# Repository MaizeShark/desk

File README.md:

# Desk

A custom-built smart L-shaped desk with deep Home Assistant integration. The project spans hardware design (custom PCBs), embedded firmware (ESP32-S3), and software services, all tied together via MQTT.

## Overview

This repository contains all the design files and software for a DIY smart desk ecosystem. The desk houses a dedicated electronics enclosure that handles audio routing, thermal management, environmental monitoring, and a media display — all controllable from Home Assistant.

```
desk/
├── PCB/            # Main KiCad PCB & schematics (ESP32-S3, DSP, DACs, PSU, …)
├── HID/            # Input device PCBs (rotary encoders, HID controller)
├── audio.md        # Audio matrix design document
├── fan_control.md  # Fan controller design document
├── Raspi/          # MPRIS-to-MQTT bridge service (Python, systemd)
└── UI/Docker/      # Media artwork generator & HTTP server (Docker)
```

---

## Sub-Projects

| | |
|---|---|
| [Audio Matrix](audio.md) | 6-in / 4-out digital audio matrix at 96 kHz / 24-bit. ADAU1451 DSP with ASRC, controlled by ESP32-S3 over I²C. Sources include USB, S/PDIF, Bluetooth (LDAC), I²S, and analog line-in. |
| [Fan Controller](fan_control.md) | ESP32-S3 reads all component temperatures via a TI TMP468 and the Raspberry Pi's CPU temp over I²C, then drives an Arctic P8 Max PWM fan based on the system hotspot. |
| [Desk GUI](https://github.com/MaizeShark/desk-gui) | ESP32-S3 firmware (PlatformIO / LVGL) for the 4-inch touchscreen control panel. Shows current track and album art, Spotify playback controls, and drives 12× addressable RGB LEDs. |
| [MPRIS → MQTT](Raspi/) | Python systemd service on the Raspberry Pi that watches the active media player via D-Bus and publishes playback state to MQTT. See [`Raspi/README.md`](Raspi/README.md). |
| [Media Artwork Service](UI/Docker/) | Dockerised service that fetches album art from Spotify / Jellyfin, composites a 480×320 image, serves it over HTTP, and publishes the URL to MQTT. See [`UI/Docker/README.md`](UI/Docker/README.md). |

---

## Hardware

The main PCB (`PCB/Tisch.kicad_pcb`) integrates all of the above subsystems onto a single board. Schematics are split into logical sheets:

| File | Content |
|---|---|
| `esp32.kicad_sch` | Main ESP32-S3 controller |
| `ADAU1451.kicad_sch` | DSP |
| `dac.kicad_sch` | PCM5122 DAC outputs |
| `adc.kicad_sch` | PCM1809 ADC input |
| `QCC5125.kicad_sch` | Bluetooth RX |
| `bm83.kicad_sch` | Bluetooth TX |
| `spdif.kicad_sch` | S/PDIF receiver |
| `raspi.kicad_sch` | Raspberry Pi interface |
| `fan.kicad_sch` | Fan control circuit |
| `psu.kicad_sch` | Power supply |
| `display.kicad_sch` | Display connector |
| `hid.kicad_sch` | HID / encoder inputs |

The `HID/` directory contains a separate PCB for the rotary encoder input device.

---

## License

This project is licensed under the **GNU General Public License v3.0**. See [`LICENSE`](LICENSE) for details.

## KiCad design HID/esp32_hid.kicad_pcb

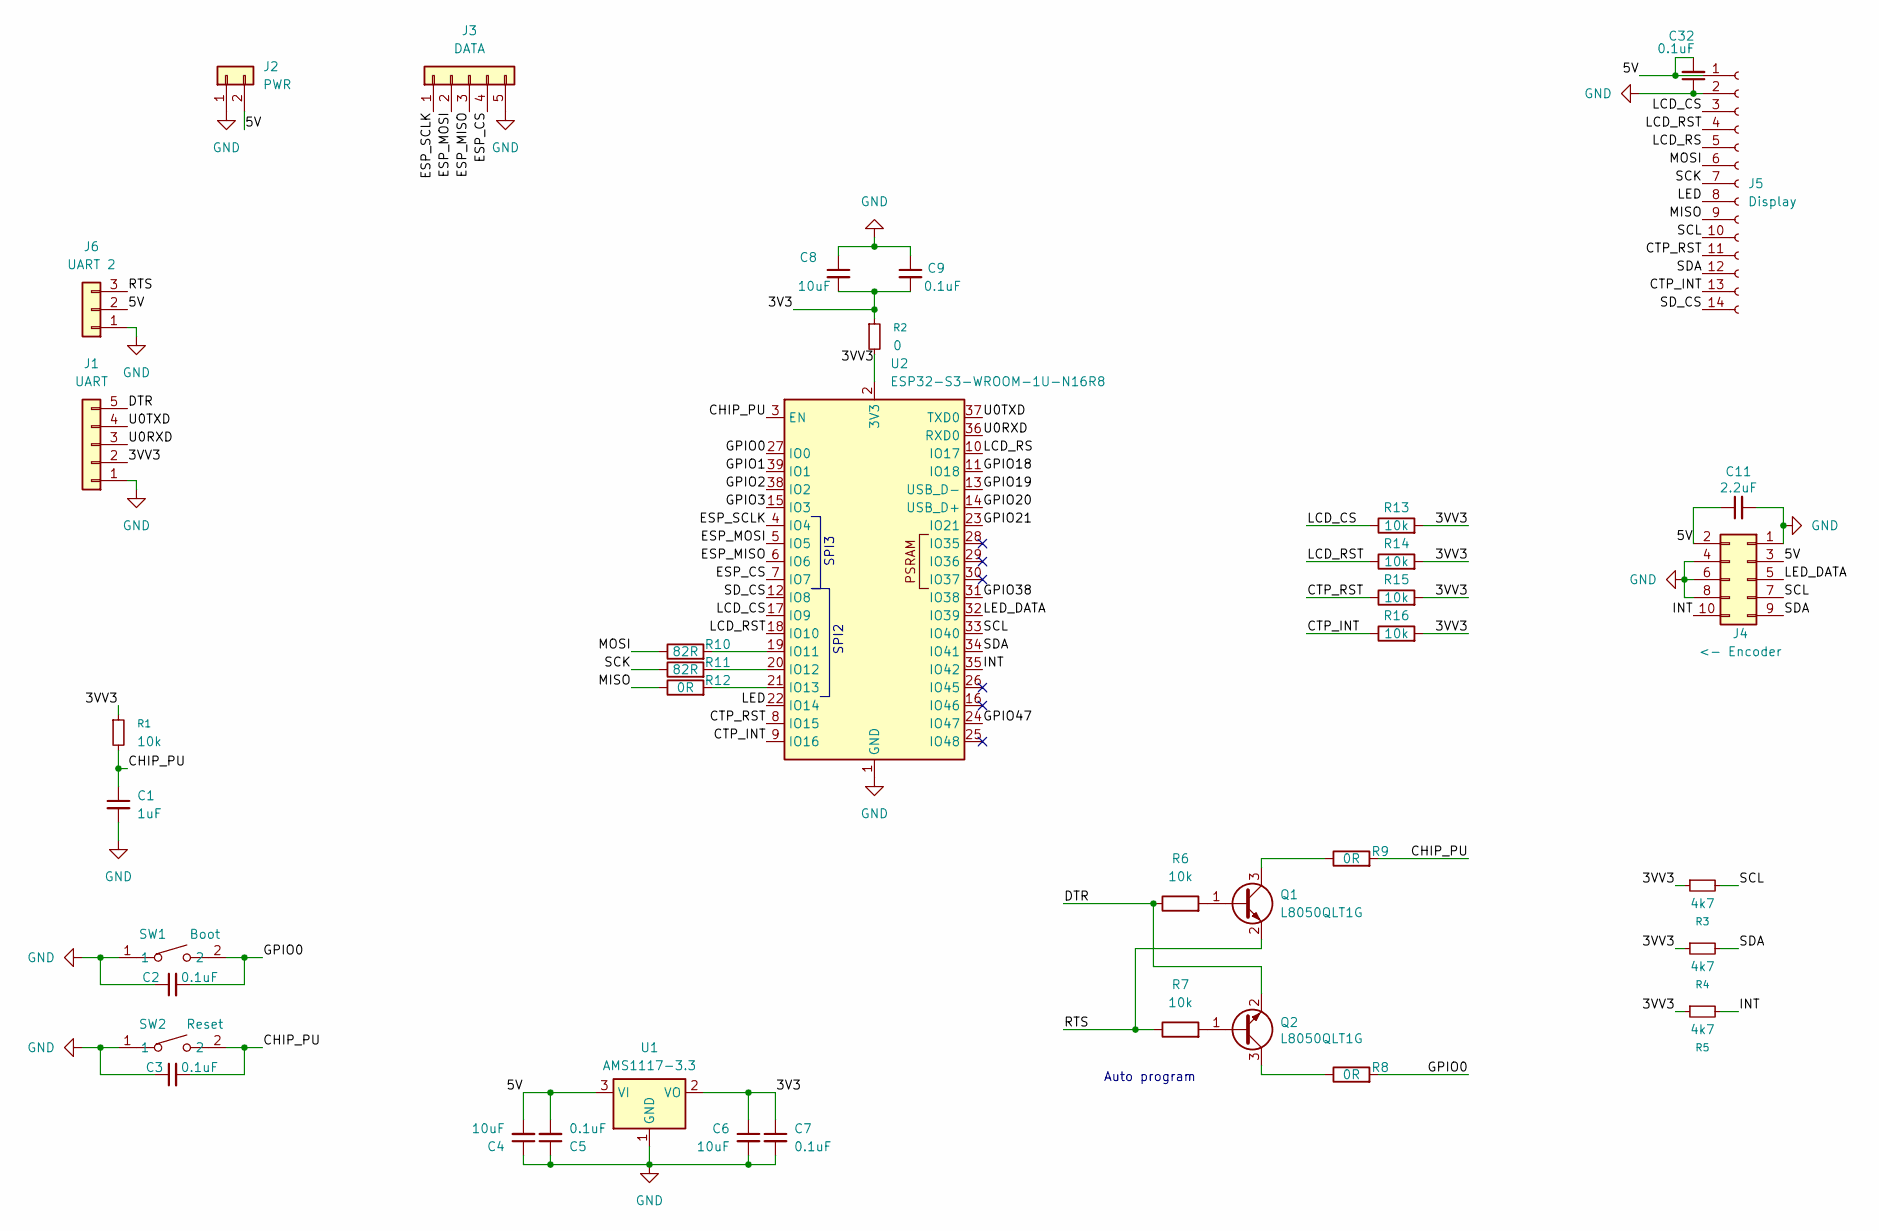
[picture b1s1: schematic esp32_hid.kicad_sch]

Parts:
C1: 1uF; C_0603_1608Metric
C2, C3, C5, C7, C9, C32: 0.1uF; C_0603_1608Metric
C4, C6, C8: 10uF; C_0805_2012Metric
C11: 2.2uF; C_0603_1608Metric
J1: UART; PinHeader_1x05_P2.54mm_Vertical
J2: PWR; JST_XH_B2B-XH-A_1x02_P2.50mm_Vertical
J3: DATA; JST_XH_B5B-XH-A_1x05_P2.50mm_Vertical
J4: <- Encoder; JST_PHD_B10B-PHDSS_2x05_P2.00mm_Vertical; LCSC C471519
J5: Display; PinSocket_1x14_P2.54mm_Vertical
J6: UART 2; PinHeader_1x03_P2.54mm_Vertical
Q1, Q2: L8050QLT1G; SOT-23; LCSC C49581
R1: 10k; R_0603_1608Metric
R2: 0; R_0603_1608Metric
R3, R4, R5: 4k7; R_0603_1608Metric
R6, R7, R13, R14, R15, R16: 10k; R_0603_1608Metric; LCSC C25804
R8, R9, R12: 0R; R_0603_1608Metric; LCSC C95177
R10, R11: 82R; R_0603_1608Metric; LCSC C23255
SW1: Boot; SW-SMD_L3.9-W3.0-P4.45; LCSC Part C720477
SW2: Reset; SW-SMD_L3.9-W3.0-P4.45; LCSC Part C720477
U1: AMS1117-3.3; SOT-223-3_TabPin2
U2: ESP32-S3-WROOM-1U-N16R8; ESP32-S3-WROOM-1

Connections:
/3V3: C6.1, C7.1, C8.2, C9.2, R2.1, U1.2 (VO)
/3VV3: J1.2, R1.1, R2.2, R3.1, R4.1, R5.1, R13.2, R14.2, R15.2, R16.2, U2.2 (3V3)
/5V: C4.2, C5.2, C11.1, C32.2, J2.2, J4.2, J4.3, J5.1, J6.2, U1.3 (VI)
/CHIP_PU: C1.1, C3.2, R1.2, R9.2, SW2.2, U2.3 (EN)
/CTP_INT: J5.13, R16.1, U2.9 (IO16)
/CTP_RST: J5.11, R15.1, U2.8 (IO15)
/DTR: J1.5, Q2.2 (E), R6.1
/ESP_CS: J3.4, U2.7 (IO7)
/ESP_MISO: J3.3, U2.6 (IO6)
/ESP_MOSI: J3.2, U2.5 (IO5)
/ESP_SCLK: J3.1, U2.4 (IO4)
/GPIO0: C2.2, R8.2, SW1.2, U2.27 (IO0)
/GPIO1: U2.39 (IO1)
/GPIO2: U2.38 (IO2)
/GPIO3: U2.15 (IO3)
/GPIO18: U2.11 (IO18)
/GPIO19: U2.13 (USB_D-)
/GPIO20: U2.14 (USB_D+)
/GPIO21: U2.23 (IO21)
/GPIO38: U2.31 (IO38)
/GPIO47: U2.24 (IO47)
/INT: J4.10, R5.2, U2.35 (IO42)
/LCD_CS: J5.3, R13.1, U2.17 (IO9)
/LCD_RS: J5.5, U2.10 (IO17)
/LCD_RST: J5.4, R14.1, U2.18 (IO10)
/LED: J5.8, U2.22 (IO14)
/LED_DATA: J4.5, U2.32 (IO39)
/MISO: J5.9, R12.1
/MOSI: J5.6, R10.1
/RTS: J6.3, Q1.2 (E), R7.1
/SCK: J5.7, R11.1
/SCL: J4.7, J5.10, R3.2, U2.33 (IO40)
/SDA: J4.9, J5.12, R4.2, U2.34 (IO41)
/SD_CS: J5.14, U2.12 (IO8)
/U0RXD: J1.3, U2.36 (RXD0)
/U0TXD: J1.4, U2.37 (TXD0)
GND: C1.2, C2.1, C3.1, C4.1, C5.1, C6.2, C7.2, C8.1, C9.1, C11.2, C32.1, J1.1, J2.1, J3.5, J4.1, J4.4, J4.6, J4.8, J5.2, J6.1, SW1.1, SW2.1, U1.1 (GND), U2.1 (GND), U2.40 (GND), U2.41 (GND)
unnamed: Q1.1 (B), R6.2
unnamed: Q1.3 (C), R9.1
unnamed: Q2.1 (B), R7.2
unnamed: Q2.3 (C), R8.1
unnamed: R10.2, U2.19 (IO11)
unnamed: R11.2, U2.20 (IO12)
unnamed: R12.2, U2.21 (IO13)

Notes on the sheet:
Auto program
SPI2
SPI3

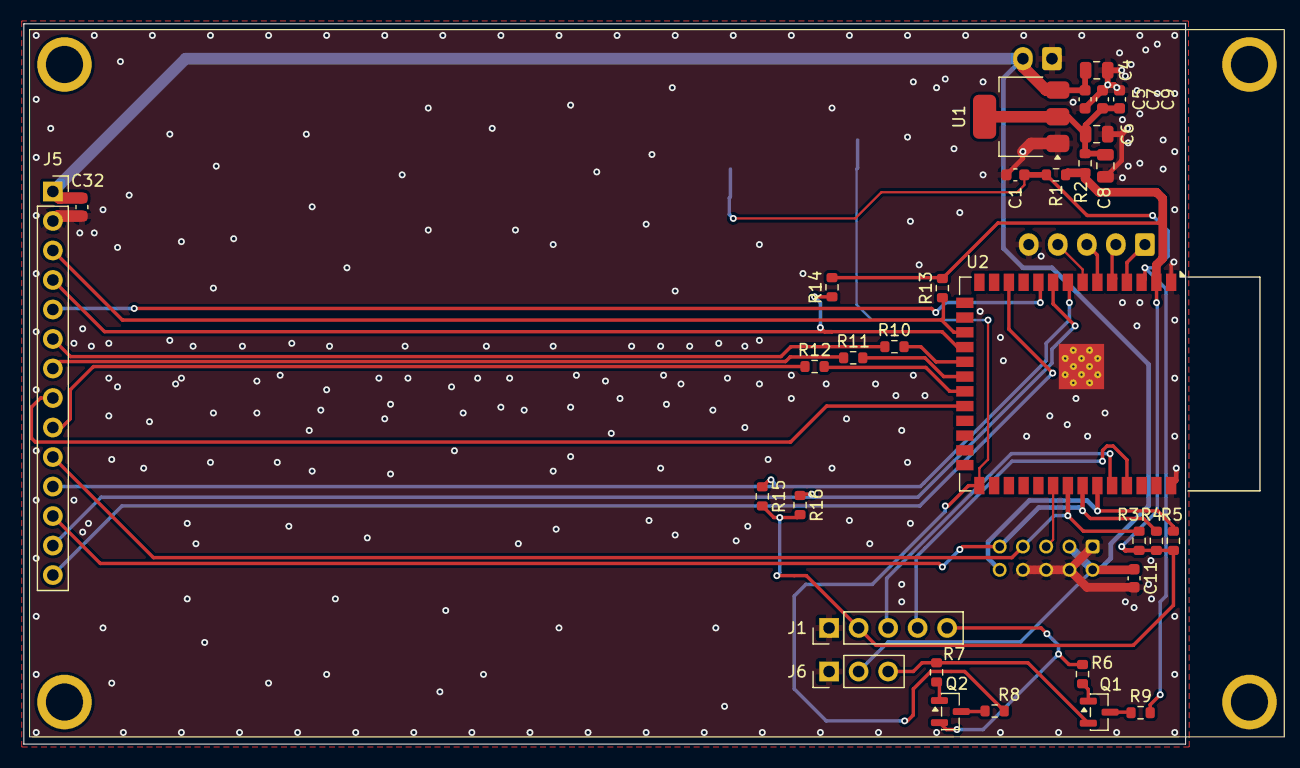
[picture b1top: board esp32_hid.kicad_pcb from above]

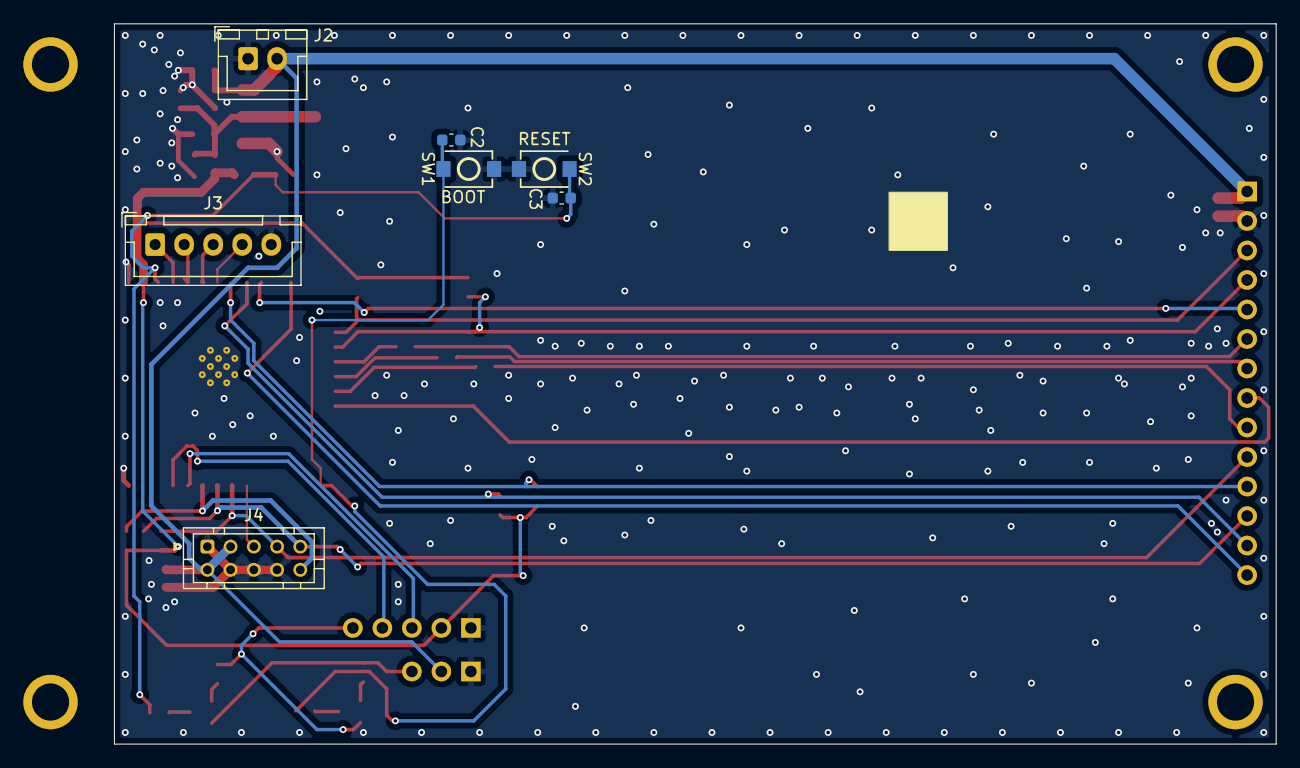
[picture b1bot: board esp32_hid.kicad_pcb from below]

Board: 2 copper layers, 100.0 x 62.0 mm, 39 parts (7 on the bottom side), 35 nets.

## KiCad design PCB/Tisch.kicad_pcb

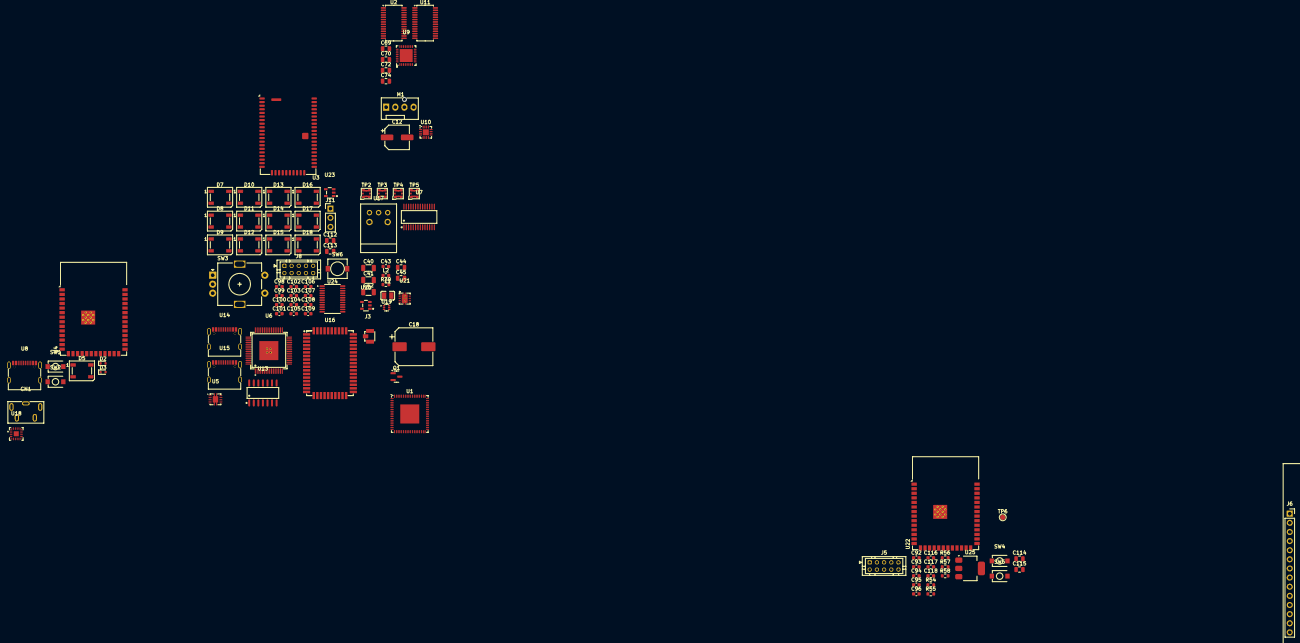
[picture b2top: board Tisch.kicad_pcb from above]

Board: 2 copper layers, 102 parts (0 on the bottom side), 82 nets, no tracks yet.

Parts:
C12: 47uF; CP_Elec_6.3x5.4
C18: 100uF; CP_Elec_10x10
C40, C41, C42: 10uF; C_1206_3216Metric
C43, C118: 2.2uF; C_0603_1608Metric
C44, C45, C112, C113, C114, C115: 10uF; C_0805_2012Metric
C69, C70, C72, C74: 2.2uF; C_0805_2012Metric
C92, C94, C95, C96, C98, C99, C100, C101, C102, C103, C104, C105, C106, C107, C108, C109, C116, C117: 0.1uF; C_0603_1608Metric
C93: 1uF; C_0603_1608Metric
CN1: PJ-358H-B; AUDIO-TH_PJ-358H-B
D2, D3: LESD5D5.0CT1G; D_SOD-523
D5, D7, D8, D9, D10, D11, D12, D13, D14, D15, D16, D17, D18: WS2812B; LED_WS2812B_PLCC4_5.0x5.0mm_P3.2mm
J3: BT1 Ant; ANT-SMD_UFL-R-SMT-1-10
J5: <- Encoder; JST_PHD_B10B-PHDSS_2x05_P2.00mm_Vertical
J6: Display; PinSocket_1x14_P2.54mm_Vertical
J8: ->ESP32; JST_PHD_B10B-PHDSS_2x05_P2.00mm_Vertical
J11: OPT; PinHeader_1x03_P2.54mm_Vertical
L1: 1uH; L0806
L2: 150nH; L_0603_1608Metric
M1: P8 Max; FanPinHeader_1x04_P2.54mm_Vertical
Q1: AO3400A; SOT-23
R30: 330m; R_0603_1608Metric
R54: 10k; R_0603_1608Metric
R55: 0; R_0603_1608Metric
R56, R57, R58: 4k7; R_0603_1608Metric
SW1, SW4: Boot; SW-SMD_L3.9-W3.0-P4.45
SW2, SW5: Reset; SW-SMD_L3.9-W3.0-P4.45
SW3: EC11E15244B2; RotaryEncoder_Alps_EC11E-Switch_Vertical_H20mm
SW6: SKSUAAE010; KEY-SMD_SKSUAAE010
TP2: spdif_error; CoaxialSwitch_Hirose_MS-156C3_Horizontal
TP3: spdif_audio; CoaxialSwitch_Hirose_MS-156C3_Horizontal
TP4: spdif_fsout0; CoaxialSwitch_Hirose_MS-156C3_Horizontal
TP5: spdif_fsout1; CoaxialSwitch_Hirose_MS-156C3_Horizontal
TP6: LED_D; TestPoint_Pad_D1.5mm
U1: ADAU1451; LFCSP-72-1EP_10x10mm_P0.5mm_EP5.3x5.3mm
U2, U11: PCM5122PW; TSSOP-28_4.4x9.7mm_P0.65mm
U3: Microchip_BM83
U4: ESP32-S3-WROOM-1
U5: TS3USB221DRCR; VSON-10_L3.0-W3.0-P0.50-TL-EP_TPS62410DRCR
U6: XU208-128-TQ64-C10; TQFP-64_L10.0-W10.0-P0.50-LS12.0-BL-EP5.3
U7: DIR9001PWR; TSSOP-28_L9.7-W4.4-P0.65-LS6.4-BL
U8, U14, U15: GT-USB-7010ASV; USB-C-SMD_G-SWITCH_GT-USB-7010ASV
U9: PCM5242RHBR; VQFN-32_L5.0-W5.0-P0.50-BL-EP
U10: TMP468xxRGT; VQFN-16-1EP_3x3mm_P0.5mm_EP1.68x1.68mm
U13: CD74HC02M96; SOIC-14_L8.7-W3.9-P1.27-LS6.0-BL
U16: BTM525; SJR-BTM525
U17: PLR237/T10BK; OPTO-TH_PLR237-T10BK
U18: PCM1809IRTER; WQFN-20_L3.0-W3.0-P0.50-TL-EP1.4
U19: TPS62A02NADRL; SOT-563
U20, U23: TPS7B92033DBVR; SOT-23-5_L2.9-W1.6-P0.95-LS2.8-BR
U21: TPS7A9401DSCR; WSON-10_L3.0-W3.0-P0.50-TL-EP
U22: ESP32-S3-WROOM-1U-N16R8; ESP32-S3-WROOM-1
U24: TCA9535PWR; TSSOP-24_4.4x7.8mm_P0.65mm
U25: AMS1117-3.3; SOT-223-3_TabPin2

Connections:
+3V3: U5.10 (VCC), U13.14 (VCC)
+5V: D5.1 (VDD), L2.1, U20.1 (IN), U21.1 (IN), U21.2 (IN)
+12V: C12.1, M1.2 (+)
/ADC/Left Audio: CN1.2 (Tip), U18.1 (IN1P)
/ADC/Right Audio: CN1.5 (Ring), U18.3 (IN2P)
/DAC/LDOO: U2.26 (LDOO), U11.26 (LDOO)
/DAC/SCL: U2.12 (SCL/MC/ATT1), U9.18 (SCL/MC/ATT1), U11.12 (SCL/MC/ATT1)
/DAC/SDA: U2.11 (SDA/MOSI/ATT2), U9.17 (SDA/MOSI/ATT2), U11.11 (SDA/MOSI/ATT2)
/ESP32/CHIP_PU: SW2.2, U4.3 (EN)
/ESP32/GPIO0: SW1.2, U4.27 (IO0)
/ESP32/GPIO19: D2.2 (A2), U4.13 (USB_D-), U8.A7 (DN1), U8.B7 (DN2)
/ESP32/GPIO20: D3.2 (A2), U4.14 (USB_D+), U8.A6 (DP1), U8.B6 (DP2)
/HID/ESP32 HID/3V3: C92.2, C94.2, C115.1, C117.1, R54.1, R55.1, U25.2 (VO)
/HID/ESP32 HID/5V: C114.2, C116.2, C118.1, J5.1, J6.1, U25.3 (VI)
/HID/ESP32 HID/CHIP_PU: C93.1, C96.2, R54.2, SW5.2, U22.3 (EN)
/HID/ESP32 HID/CTP_INT: J6.13, U22.9 (IO16)
/HID/ESP32 HID/CTP_RST: J6.11, U22.8 (IO15)
/HID/ESP32 HID/GPIO0: C95.2, SW4.2
/HID/ESP32 HID/INT: J5.9, R58.2, U22.35 (IO42)
/HID/ESP32 HID/LCD_CS: J6.3, U22.17 (IO9)
/HID/ESP32 HID/LCD_RST: J6.4, U22.18 (IO10)
/HID/ESP32 HID/LED: J6.8, U22.22 (IO14)
/HID/ESP32 HID/LED_DATA: J5.3, TP6.1, U22.32 (IO39)
/HID/ESP32 HID/MISO: J6.9, U22.19 (IO11)
/HID/ESP32 HID/MOSI: J6.6, U22.20 (IO12)
/HID/ESP32 HID/SCK: J6.7, U22.21 (IO13)
/HID/ESP32 HID/SCL: J5.5, J6.10, R56.2, U22.33 (IO40)
/HID/ESP32 HID/SDA: J5.7, J6.12, R57.2, U22.34 (IO41)
/HID/ESP32 HID/SD_CS: J6.14, U22.12 (IO8)
/HID/ESP32 HID/VCC_3V3: R56.1, R57.1, R58.1
/HID/Encoder/3V3: C113.1, U23.5 (OUT)
/HID/Encoder/5V: C98.1, C99.1, C100.1, C101.1, C102.1, C103.1, C104.1, C105.1, C106.1, C107.1, C108.1, C109.1, C112.2, D7.1 (VDD), D8.1 (VDD), D9.1 (VDD), D10.1 (VDD), D11.1 (VDD), D12.1 (VDD), D13.1 (VDD), D14.1 (VDD), D15.1 (VDD), D16.1 (VDD), D17.1 (VDD), D18.1 (VDD), J8.1, U23.1 (IN)
/HID/Encoder/INT: J8.9, U24.1 (~INT)
/HID/Encoder/LED_DATA: D7.4 (DIN), J8.3
/HID/Encoder/SCL: J8.5, U24.22 (SCL)
/HID/Encoder/SDA: J8.7, U24.23 (SDA)
/HID/Encoder/back_sw: SW6.1, U24.7 (P03)
/HID/Encoder/rot_a: SW3.A, U24.4 (P00)
/HID/Encoder/rot_b: SW3.B, U24.5 (P01)
/HID/Encoder/rot_sw: SW3.S1, U24.6 (P02)
/QCC5125/RF_ANT_50R: J3.1 (In), U16.46 (RF)
/SPdif/SPDIF: U7.20 (RXIN), U17.3 (VOUT)
/USB audio/1D+: U5.1 (1D+), U14.A6 (DP1), U14.B6 (DP2)
/USB audio/1D-: U5.2 (1D-), U14.A7 (DN1), U14.B7 (DN2)
/USB audio/2D+: U5.3 (2D+), U15.A6 (DP1), U15.B6 (DP2)
/USB audio/2D-: U5.4 (2D-), U15.A7 (DN1), U15.B7 (DN2)
AVDD_3V3: C72.1, U2.8 (AVDD), U7.24 (VCC), U9.5 (CPVDD), U9.14 (AVDD), U11.8 (AVDD), U17.1 (VCC), U18.16 (AVDD), U21.8 (SNS), U21.9 (OUT), U21.10 (OUT)
DVDD_3V3: C40.1, C41.1, C42.1, L1.2, U2.18 (MODE2/MS), U2.28 (DVDD), U3.23 (BAT_IN), U9.22 (ADR2/GPIO2/GPO), U9.24 (MODE2/MS), U11.16 (ADR2/GPIO2/DOUT), U11.18 (MODE2/MS), U11.24 (ADR1/MISO/FMT), U11.28 (DVDD), U19.6 (OUT)
GND: C12.2, C18.2, C40.2, C41.2, C42.2, C43.2, C44.2, C45.2, C70.1, C72.2, C74.1, C92.1, C93.2, C94.1, C95.1, C96.1, C98.2, C99.2, C100.2, C101.2, C102.2, C103.2, C104.2, C105.2, C106.2, C107.2, C108.2, C109.2, C112.1, C113.2, C114.1, C115.2, C116.1, C117.2, C118.2, CN1.3 (TSW), D2.1 (A1), D3.1 (A1), D5.3 (VSS), D7.3 (VSS), D8.3 (VSS), D9.3 (VSS), D10.3 (VSS), D11.3 (VSS), D12.3 (VSS), D13.3 (VSS), D14.3 (VSS), D15.3 (VSS), D16.3 (VSS), D17.3 (VSS), D18.3 (VSS), J3.2 (Ext), J5.2, J5.4, J5.6, J5.8, J5.10, J6.2, J8.2, J8.4, J8.6, J8.8, J8.10, M1.1 (-), Q1.2 (S), SW1.1, SW2.1, SW3.C, SW3.MP, SW3.S2, SW4.1, SW5.1, SW6.2, U2.3 (CPGND), U2.9 (AGND), U2.16 (ADR2/GPIO2/DOUT), U2.17 (MODE1), U2.24 (ADR1/MISO/FMT), U2.27 (DGND), U3.16 (GND), U3.50 (GND), U3.56 (GND), U3.57 (GND), U4.1 (GND), U4.40 (GND), U4.41 (GND), U5.5 (GND), U5.11, U7.6 (DGND), U7.13 (PSCK0), U7.14 (PSCK1), U7.19 (RSV), U7.23 (AGND), U7.28 (CKSEL), U8.1 (SHELL), U8.2 (SHELL), U8.3 (SHELL), U8.4 (SHELL), U9.3 (DGND), U9.7 (CPGND), U9.15 (AGND), U9.23 (MODE1), U9.32 (ADR1/MISO/FMT), U9.33 (PAD), U10.8 (GND), U10.9 (ADD), U10.17 (GND), U11.3 (CPGND), U11.9 (AGND), U11.17 (MODE1), U11.27 (DGND), U13.5 (2A), U13.6 (2B), U13.7 (GND), U13.8 (3A), U13.9 (3B), U13.11 (4A), U13.12 (4B), U16.15 (GND), U16.21 (GND), U16.38 (GND), U16.44 (GND), U16.45 (GND), U16.47 (GND), U17.2 (GND), U18.2 (IN1M), U18.4 (IN2M), U18.5 (VSS), U18.10 (VSS), U18.11 (MD1), U18.12 (MD0), U18.13 (MSZ), U18.15 (VSS), U18.19 (FMT0), U18.20 (VSS), U18.21 (EP), U19.1 (GND), U20.2 (GND), U21.4 (PG), U21.6 (GND), U21.11 (EP), U22.1 (GND), U22.40 (GND), U22.41 (GND), U23.2 (GND), U24.2 (A1), U24.3 (A2), U24.12 (GND), U24.21 (A0), U25.1 (GND)
IOVDD_3V3: C70.2, U2.1 (CPVDD), U7.5 (VDD), U9.4 (DVDD), U10.14 (V+), U11.1 (CPVDD), U16.7 (VBAT_SENSE), U16.14 (VBAT), U16.23 (VDD_PADS1), U16.24 (VDD_PADS3_7), U18.9 (IOVDD), U20.5 (OUT)
unnamed: C44.1, R30.2
unnamed: D7.2 (DOUT), D8.4 (DIN)
unnamed: D8.2 (DOUT), D9.4 (DIN)
unnamed: D9.2 (DOUT), D10.4 (DIN)
unnamed: D10.2 (DOUT), D11.4 (DIN)
unnamed: D11.2 (DOUT), D12.4 (DIN)
unnamed: D12.2 (DOUT), D13.4 (DIN)
unnamed: D13.2 (DOUT), D14.4 (DIN)
unnamed: D14.2 (DOUT), D15.4 (DIN)
unnamed: D15.2 (DOUT), D16.4 (DIN)
unnamed: D16.2 (DOUT), D17.4 (DIN)
unnamed: D17.2 (DOUT), D18.4 (DIN)
unnamed: J11.1, U24.8 (P04)
unnamed: J11.2, U24.9 (P05)
unnamed: J11.3, U24.10 (P06)
unnamed: U1.1 (DGND), U1.17 (DGND), U1.19 (DGND), U1.25 (DGND), U1.36 (DGND), U1.37 (DGND), U1.54 (DGND), U1.55 (DGND), U1.72 (DGND)
unnamed: U1.20 (DVDD), U1.35 (DVDD), U1.53 (DVDD), U1.71 (DVDD)
unnamed: U1.2 (IOVDD), U1.18 (IOVDD), U1.38 (IOVDD), U1.56 (IOVDD)
unnamed: C69.1, U9.8 (CAPM)
unnamed: C69.2, U9.6 (CAPP)
unnamed: C74.2, U9.9 (VNEG)
unnamed: U10.1 (D6+), U10.2 (D5+), U10.3 (D4+), U10.4 (D3+), U10.5 (D2+), U10.6 (D1+), U10.7 (D-), U10.15 (D8+), U10.16 (D7+)
unnamed: U5.9 (S), U13.3 (1B)
unnamed: U5.6 (~OE), U13.1 (1Y)
unnamed: U14.3 (SHELL), U14.4 (SHELL)
unnamed: U14.1 (SHELL), U14.2 (SHELL)
unnamed: U15.3 (SHELL), U15.4 (SHELL)
unnamed: U15.1 (SHELL), U15.2 (SHELL)
unnamed: C43.1, C45.1, L2.2, R30.1, U19.3 (VIN), U19.4 (EN)
unnamed: L1.1, U19.2 (SW)
unnamed: R55.2, U22.2 (3V3)
VBUS: U16.10 (VCHG), U16.11 (VCHG_SENSE)

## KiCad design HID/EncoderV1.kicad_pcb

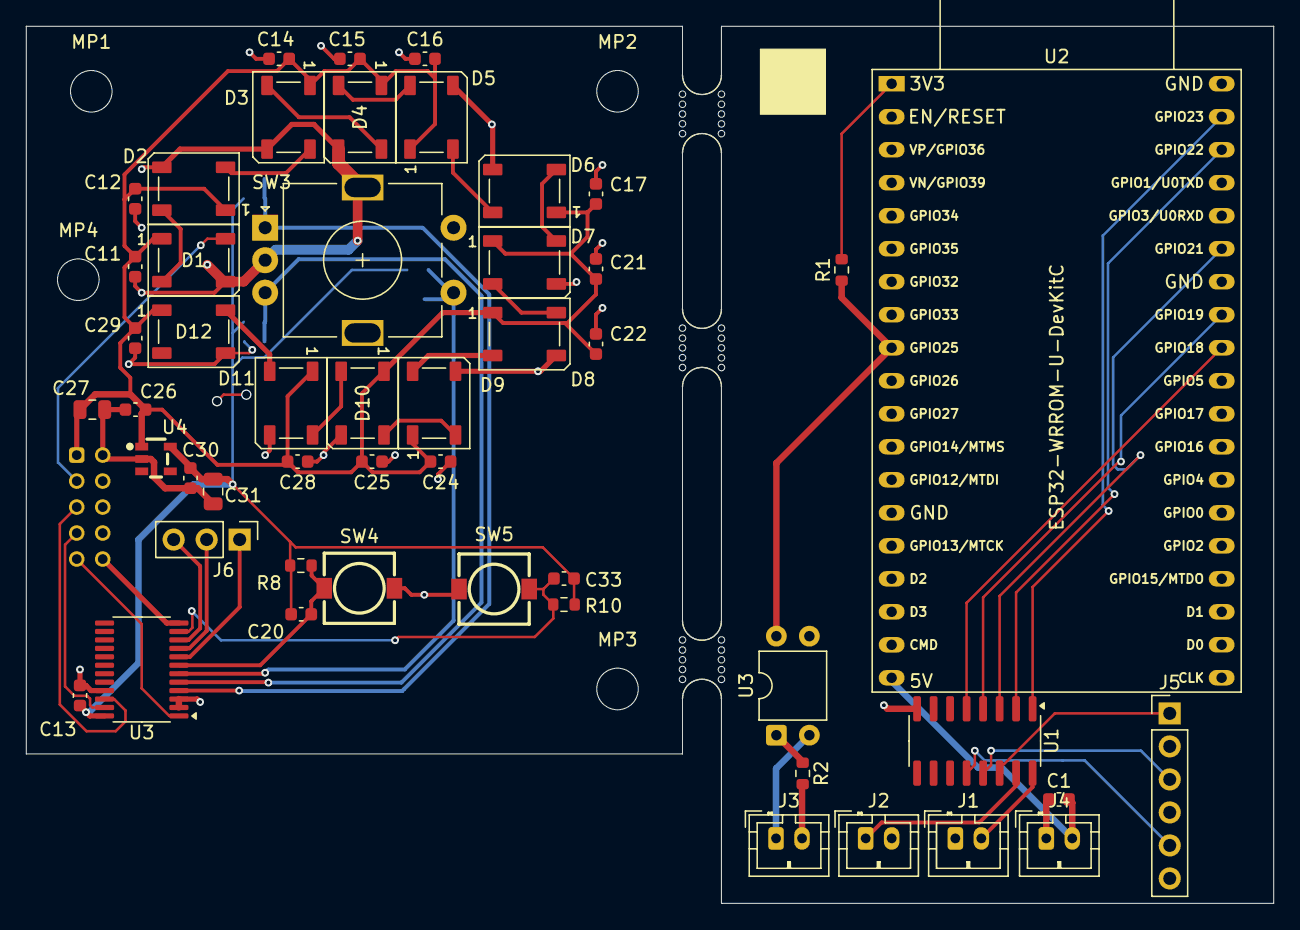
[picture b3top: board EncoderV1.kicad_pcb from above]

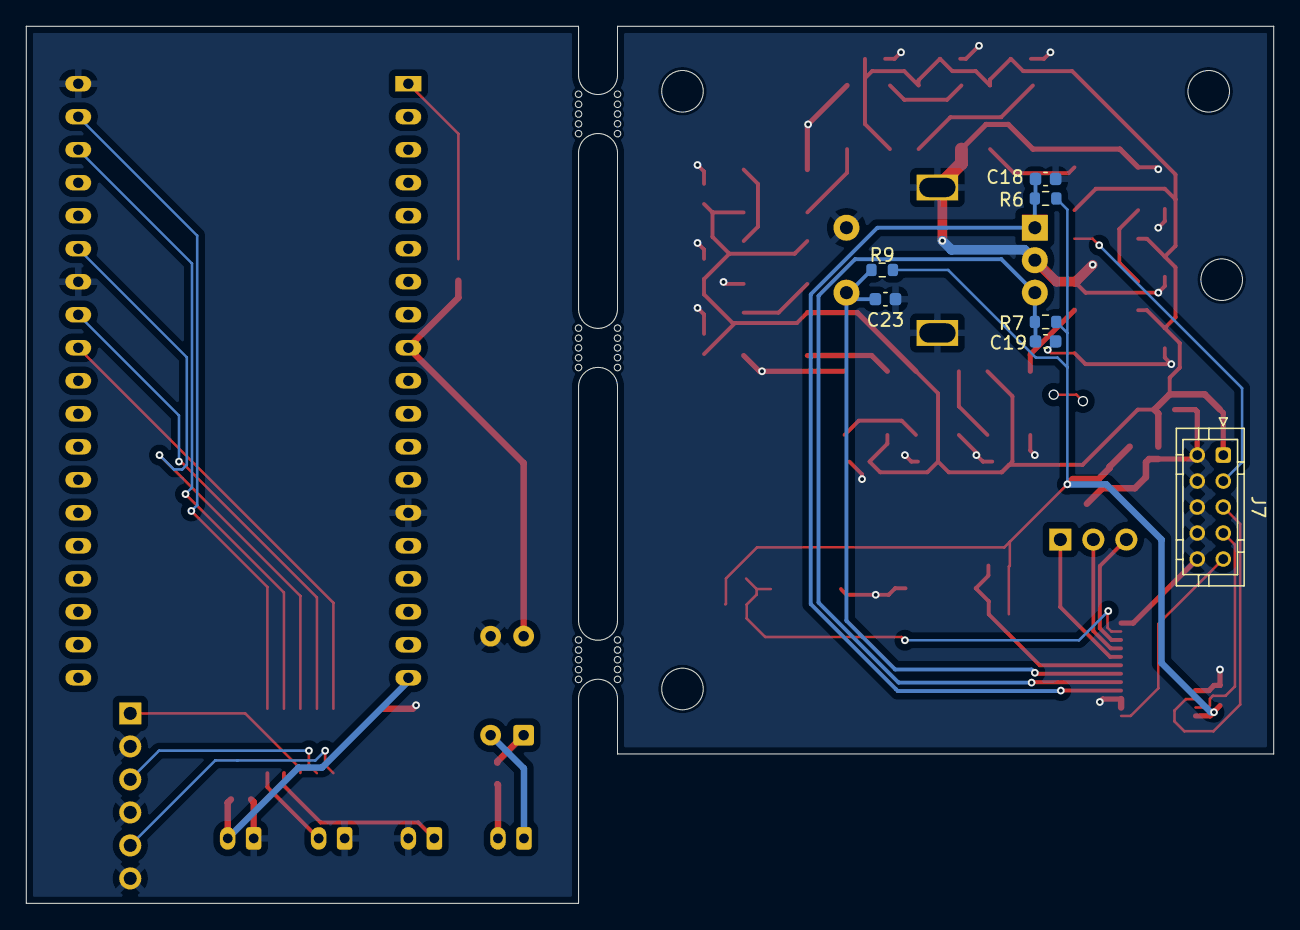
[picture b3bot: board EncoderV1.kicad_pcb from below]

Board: 2 copper layers, 96.0 x 67.5 mm, 64 parts (7 on the bottom side), 42 nets.

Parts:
C1: 10uF; C_0603_1608Metric
C11, C12, C13, C14, C15, C16, C17, C18, C19, C20, C21, C22, C23, C24, C25, C26, C28, C29, C30, C33: 0.1uF; C_0603_1608Metric
C27, C31: 10uF; C_0805_2012Metric
D1, D2, D3, D4, D5, D6, D7, D8, D9, D10, D11, D12: WS2812B; LED_WS2812B_PLCC4_5.0x5.0mm_P3.2mm
J1: POWER_BTN; JST_PH_B2B-PH-K_1x02_P2.00mm_Vertical
J2: AUX1; JST_PH_B2B-PH-K_1x02_P2.00mm_Vertical
J3: POWER_LED; JST_PH_B2B-PH-K_1x02_P2.00mm_Vertical
J4: POWER; JST_PH_B2B-PH-K_1x02_P2.00mm_Vertical
J5: OPT; PinHeader_1x06_P2.54mm_Vertical
J6: OPT; PinHeader_1x03_P2.54mm_Vertical
J7: ->ESP32; JST_PHD_B10B-PHDSS_2x05_P2.00mm_Vertical
MP1, MP2, MP3, MP4: MountingHole_3.2mm_M3_ISO7380
R1: 4k7; R_0603_1608Metric
R2: 220R; R_0603_1608Metric
R6, R7, R8, R9, R10: 10k; R_0603_1608Metric
SW3: EC11E15244B2; RotaryEncoder_Alps_EC11E-Switch_Vertical_H20mm
SW4, SW5: SKSUAAE010; KEY-SMD_SKSUAAE010
U1: ULN2003A; SOIC-16_3.9x9.9mm_P1.27mm
U2: ESP32-WRROM-U-DevKitC; ESP32-DevKitC
U3: PC817; DIP-4_W7.62mm
U3#2: TCA9535PWR; TSSOP-24_4.4x7.8mm_P0.65mm
U4: TPS7B92033DBVR; SOT-23-5_L2.9-W1.6-P0.95-LS2.8-BR
mouse-bite-3mm-slot, mouse-bite-3mm-slot#2, mouse-bite-3mm-slot#3: VAL**; mouse-bite-3mm-slot

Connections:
+3V3: R1.2, U2.1 (3V3)
+5V: C1.2, J4.2, U2.19 (5V)
/Encoder/3V3: C13.2, C20.1, C30.1, C31.1, C33.1, R6.1, R7.1, R8.1, R9.1, R10.1, U3#2.24 (VCC), U4.5 (OUT)
/Encoder/5V: C11.1, C12.1, C14.1, C15.1, C16.1, C17.1, C21.1, C22.1, C24.1, C25.1, C26.1, C27.2, C28.1, C29.1, D1.1 (VDD), D2.1 (VDD), D3.1 (VDD), D4.1 (VDD), D5.1 (VDD), D6.1 (VDD), D7.1 (VDD), D8.1 (VDD), D9.1 (VDD), D10.1 (VDD), D11.1 (VDD), D12.1 (VDD), J7.1, U4.1 (IN)
/Encoder/INT: J7.9, U3#2.1 (~INT)
/Encoder/LED_DATA: D1.4 (DIN), J7.3
/Encoder/SCL: J7.5, U3#2.22 (SCL)
/Encoder/SDA: J7.7, U3#2.23 (SDA)
/Encoder/back_sw: C20.2, R8.2, SW4.1, U3#2.7 (P03)
/Encoder/rot_a: C18.2, R6.2, SW3.A, U3#2.4 (P00)
/Encoder/rot_b: C19.2, R7.2, SW3.B, U3#2.5 (P01)
/Encoder/rot_sw: C23.2, R9.2, SW3.S1, U3#2.6 (P02)
/Encoder/sw_2: C33.2, R10.2, SW5.1, U3#2.11 (P07)
/IN1: U1.1 (I1), U2.37 (GPIO23)
/IN2: U1.2 (I2), U2.36 (GPIO22)
/IN3: U1.3 (I3), U2.33 (GPIO21)
/IN4: U1.4 (I4), U2.31 (GPIO19)
/IN5: U1.5 (I5), U2.30 (GPIO18)
GND: C1.1, C11.2, C12.2, C13.1, C14.2, C15.2, C16.2, C17.2, C18.1, C19.1, C21.2, C22.2, C23.1, C24.2, C25.2, C26.2, C27.1, C28.2, C29.2, C30.2, C31.2, D1.3 (VSS), D2.3 (VSS), D3.3 (VSS), D4.3 (VSS), D5.3 (VSS), D6.3 (VSS), D7.3 (VSS), D8.3 (VSS), D9.3 (VSS), D10.3 (VSS), D11.3 (VSS), D12.3 (VSS), J1.1, J2.2, J4.1, J5.2, J5.4, J5.6, J7.2, J7.4, J7.6, J7.8, J7.10, SW3.C, SW3.MP, SW3.S2, SW4.2, SW5.2, U1.8 (GND), U2.14 (GND), U2.32 (GND), U2.38 (GND), U3.3, U3#2.2 (A1), U3#2.3 (A2), U3#2.12 (GND), U3#2.21 (A0), U4.2 (GND)
unnamed: D1.2 (DOUT), D2.4 (DIN)
unnamed: D2.2 (DOUT), D3.4 (DIN)
unnamed: D3.2 (DOUT), D4.4 (DIN)
unnamed: D4.2 (DOUT), D5.4 (DIN)
unnamed: D5.2 (DOUT), D6.4 (DIN)
unnamed: D6.2 (DOUT), D7.4 (DIN)
unnamed: D7.2 (DOUT), D8.4 (DIN)
unnamed: D8.2 (DOUT), D9.4 (DIN)
unnamed: D9.2 (DOUT), D10.4 (DIN)
unnamed: D10.2 (DOUT), D11.4 (DIN)
unnamed: D11.2 (DOUT), D12.4 (DIN)
unnamed: J1.2, U1.16 (O1)
unnamed: J2.1, U1.15 (O2)
unnamed: J3.1, U3.2
unnamed: J3.2, R2.2
unnamed: J5.1, U1.14 (O3)
unnamed: J5.3, U1.13 (O4)
unnamed: J5.5, U1.12 (O5)
unnamed: J6.1, U3#2.8 (P04)
unnamed: J6.2, U3#2.9 (P05)
unnamed: J6.3, U3#2.10 (P06)
unnamed: R2.1, U3.1
unnamed: R1.1, U2.9 (DAC_1/ADC2_CH8/GPIO25), U3.4

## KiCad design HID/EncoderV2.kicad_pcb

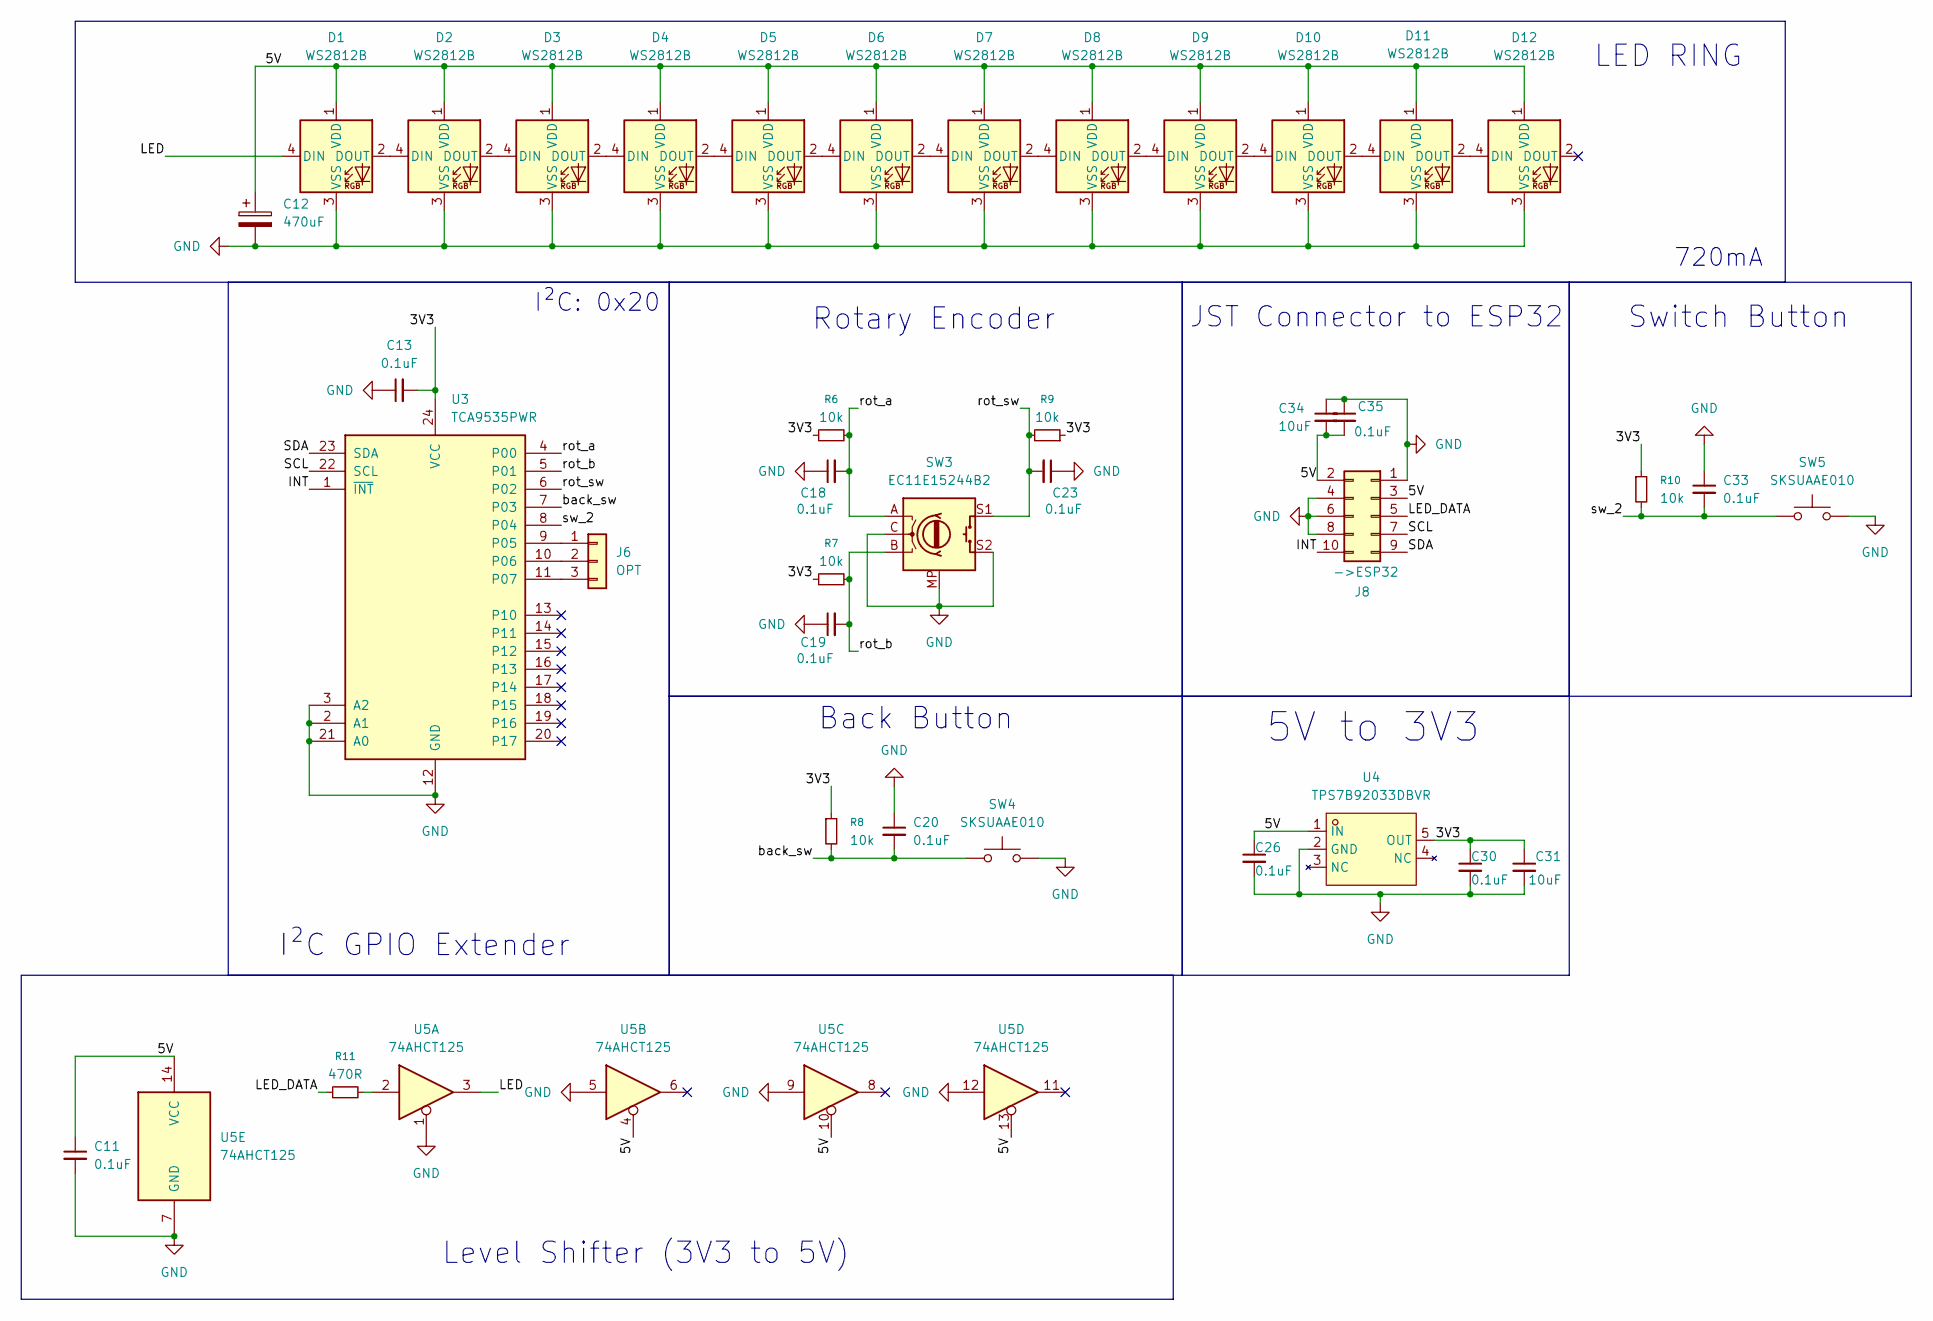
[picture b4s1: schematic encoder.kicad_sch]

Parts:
C11, C13, C18, C19, C20, C23, C26, C30, C33, C35: 0.1uF; C_0603_1608Metric
C12: 470uF; CP_Elec_6.3x7.7
C31, C34: 10uF; C_0805_2012Metric
D1, D2, D3, D4, D5, D6, D7, D8, D9, D10, D12: WS2812B; LED_WS2812B_PLCC4_5.0x5.0mm_P3.2mm; LCSC C2874885
D11: WS2812B; LED_WS2812B_PLCC4_5.0x5.0mm_P3.2mm
J6: OPT; PinHeader_1x03_P2.54mm_Vertical
J8: ->ESP32; JST_PHD_B10B-PHDSS_2x05_P2.00mm_Vertical; LCSC C471519
R6, R7, R8, R9, R10: 10k; R_0603_1608Metric
R11: 470R; R_0603_1608Metric
SW3: EC11E15244B2; RotaryEncoder_Alps_EC11E-Switch_Vertical_H20mm
SW4, SW5: SKSUAAE010; KEY-SMD_SKSUAAE010
U3: TCA9535PWR; TSSOP-24_4.4x7.8mm_P0.65mm
U4: TPS7B92033DBVR; SOT-23-5_L2.9-W1.6-P0.95-LS2.8-BR; LCSC Part C32353919
U5: 74AHCT125; VQFN-14_L3.5-W3.5-P0.50-BL-EP; LCSC C2675532

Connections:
/Encoder/3V3: C13.2, C30.1, C31.1, R6.1, R7.1, R8.1, R9.1, R10.1, U3.24 (VCC), U4.5 (OUT)
/Encoder/5V: C11.1, C12.1, C26.1, C34.2, C35.2, D1.1 (VDD), D2.1 (VDD), D3.1 (VDD), D4.1 (VDD), D5.1 (VDD), D6.1 (VDD), D7.1 (VDD), D8.1 (VDD), D9.1 (VDD), D10.1 (VDD), D11.1 (VDD), D12.1 (VDD), J8.2, J8.3, U4.1 (IN), U5.4, U5.10, U5.13, U5.14 (VCC)
/Encoder/INT: J8.10, U3.1 (~INT)
/Encoder/LED: D1.4 (DIN), U5.3
/Encoder/LED_DATA: J8.5, R11.1
/Encoder/SCL: J8.7, U3.22 (SCL)
/Encoder/SDA: J8.9, U3.23 (SDA)
/Encoder/back_sw: C20.2, R8.2, SW4.1, U3.7 (P03)
/Encoder/rot_a: C18.2, R6.2, SW3.A, U3.4 (P00)
/Encoder/rot_b: C19.2, R7.2, SW3.B, U3.5 (P01)
/Encoder/rot_sw: C23.2, R9.2, SW3.S1, U3.6 (P02)
/Encoder/sw_2: C33.2, R10.2, SW5.1, U3.8 (P04)
GND: C11.2, C12.2, C13.1, C18.1, C19.1, C20.1, C23.1, C26.2, C30.2, C31.2, C33.1, C34.1, C35.1, D1.3 (VSS), D2.3 (VSS), D3.3 (VSS), D4.3 (VSS), D5.3 (VSS), D6.3 (VSS), D7.3 (VSS), D8.3 (VSS), D9.3 (VSS), D10.3 (VSS), D11.3 (VSS), D12.3 (VSS), J8.1, J8.4, J8.6, J8.8, SW3.C, SW3.MP, SW3.S2, SW4.2, SW5.2, U3.2 (A1), U3.3 (A2), U3.12 (GND), U3.21 (A0), U4.2 (GND), U5.1, U5.5, U5.7 (GND), U5.9, U5.12; also elsewhere on the board
unnamed: D1.2 (DOUT), D2.4 (DIN)
unnamed: D2.2 (DOUT), D3.4 (DIN)
unnamed: D3.2 (DOUT), D4.4 (DIN)
unnamed: D4.2 (DOUT), D5.4 (DIN)
unnamed: D5.2 (DOUT), D6.4 (DIN)
unnamed: D6.2 (DOUT), D7.4 (DIN)
unnamed: D7.2 (DOUT), D8.4 (DIN)
unnamed: D8.2 (DOUT), D9.4 (DIN)
unnamed: D9.2 (DOUT), D10.4 (DIN)
unnamed: D10.2 (DOUT), D11.4 (DIN)
unnamed: D11.2 (DOUT), D12.4 (DIN)
unnamed: J6.1, U3.9 (P05)
unnamed: J6.2, U3.10 (P06)
unnamed: J6.3, U3.11 (P07)
unnamed: R11.2, U5.2

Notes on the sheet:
I²C: 0x20
JST Connector to ESP32
LED RING
I²C GPIO Extender
Rotary Encoder
720mA
Back Button
5V to 3V3
Switch Button
Level Shifter (3V3 to 5V)
